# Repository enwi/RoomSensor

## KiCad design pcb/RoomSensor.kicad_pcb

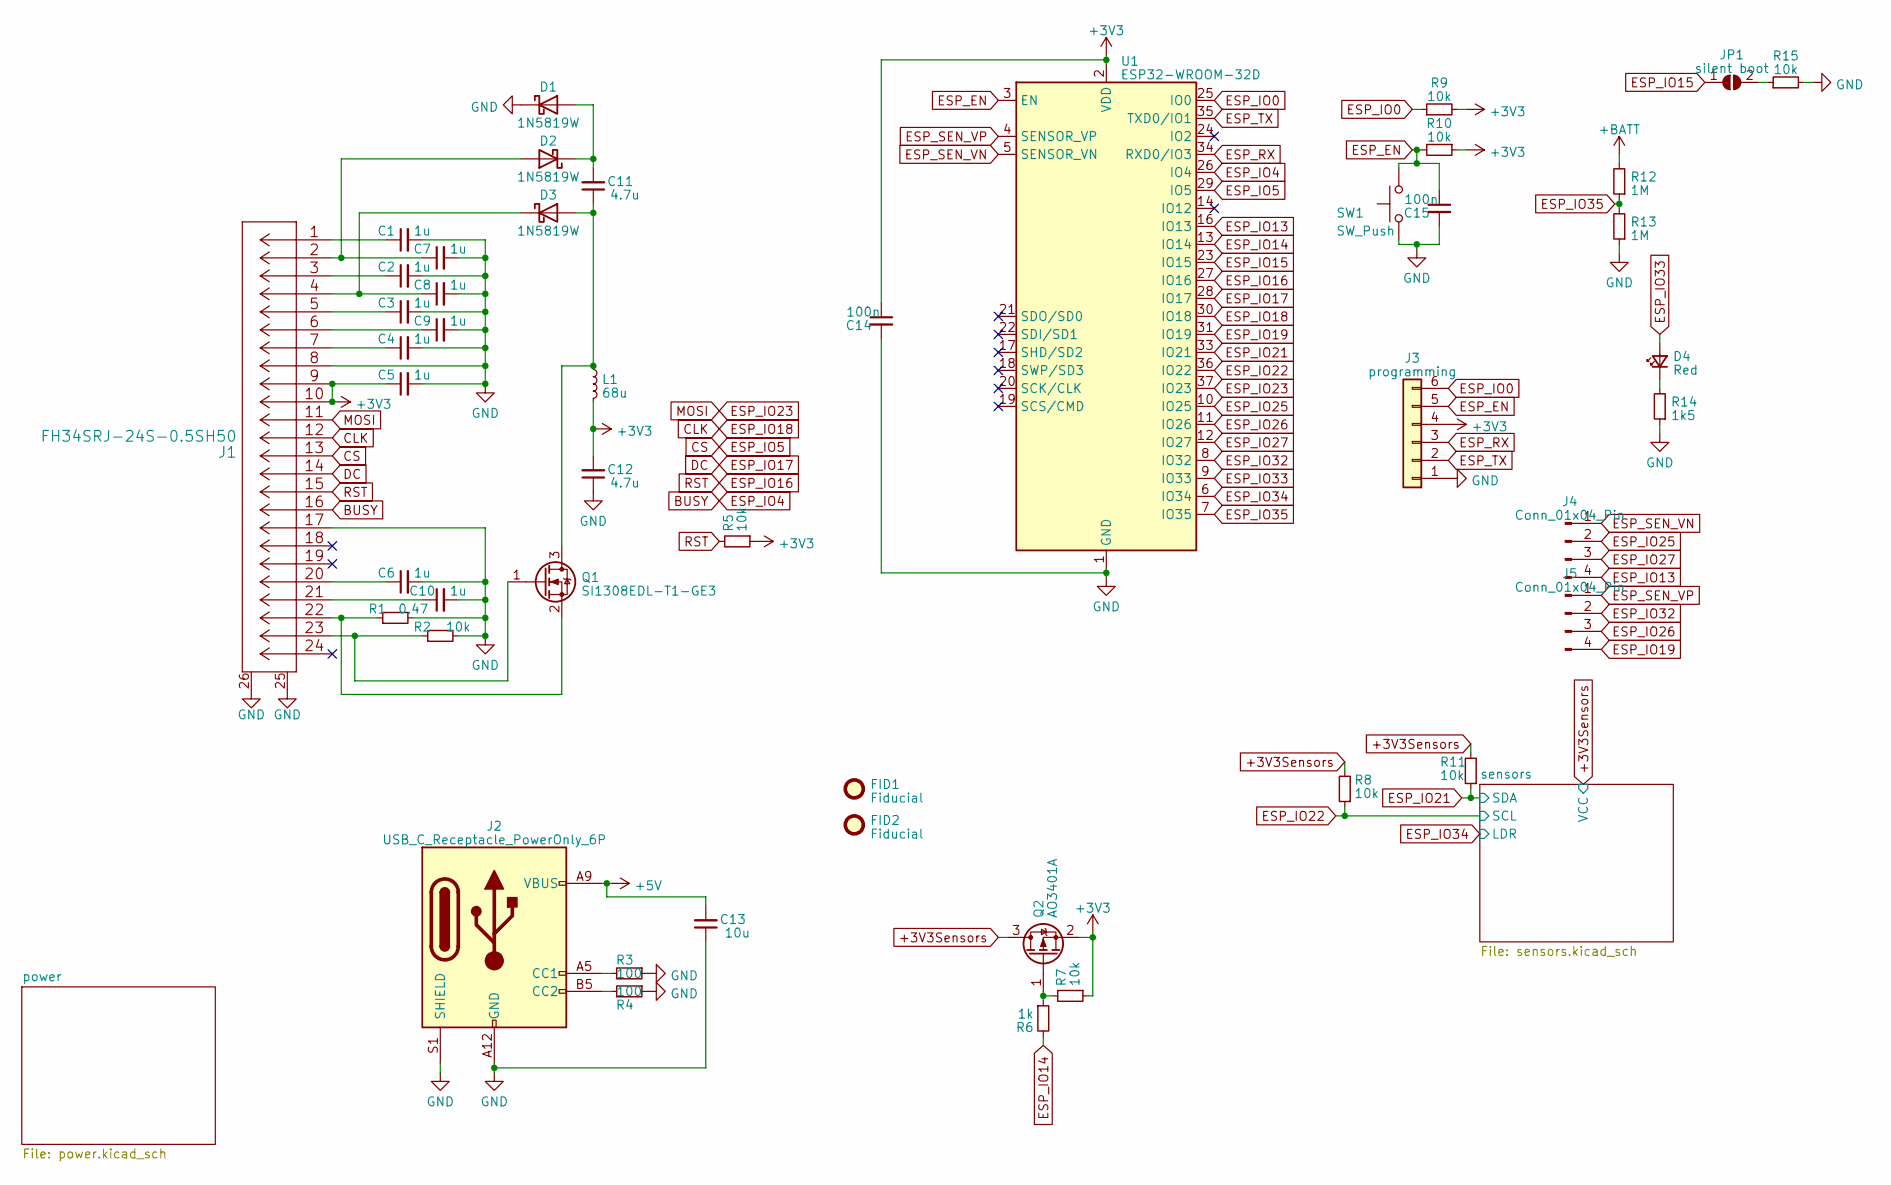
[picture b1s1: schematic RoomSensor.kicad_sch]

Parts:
C1, C2, C3, C4, C5, C6, C7, C8, C9, C10: 1u; C_0603_1608Metric
C11, C12: 4.7u; C_0603_1608Metric
C13: 10u; C_0603_1608Metric
C14, C15: 100n; C_0603_1608Metric
D1, D2, D3: 1N5819W; D_SOD-323
D4: Red; LED_0603_1608Metric
FID1, FID2: Fiducial; Fiducial_0.5mm_Mask1.5mm
J1: FH34SRJ-24S-0.5SH50
J2: USB_C_Receptacle_PowerOnly_6P; TYPE-C 6P LCH10.0
J3: programming; PinSocket_1x06_P2.54mm_Vertical
J4, J5: Conn_01x04_Pin; PinHeader_1x04_P2.54mm_Vertical
JP1: silent boot; SolderJumper-2_P1.3mm_Open_TrianglePad1.0x1.5mm
L1: 68u; L_0805_2012Metric_Pad1.15x1.40mm_HandSolder
Q1: SI1308EDL-T1-GE3; SOT-323_SC-70
Q2: AO3401A; SOT-23
R1: 0.47; R_0603_1608Metric
R2, R5, R7, R8, R9, R10, R11, R15: 10k; R_0603_1608Metric
R3, R4: 100; R_0603_1608Metric
R6: 1k; R_0603_1608Metric
R12, R13: 1M; R_0603_1608Metric
R14: 1k5; R_0603_1608Metric
SW1: SW_Push; TSB001A3826A
U1: ESP32-WROOM-32D

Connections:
+3V3: C5.1, C12.2, C14.1, J1.9, J1.10, J3.4, L1.2, Q2.2 (S), R5.1, R7.1, R9.2, R10.1, U1.2 (VDD); also elsewhere on the board
+3V3Sensors: Q2.3 (D), R8.2, R11.2; also elsewhere on the board
+5V: C13.2, J2.A9 (VBUS), J2.B9 (VBUS); also elsewhere on the board
+BATT: R12.2; also elsewhere on the board
BUSY: J1.16, U1.26 (IO4)
CLK: J1.12, U1.30 (IO18)
CS: J1.13, U1.29 (IO5)
DC: J1.14, U1.28 (IO17)
ESP_EN: C15.1, J3.5, R10.2, SW1.2, U1.3 (EN)
ESP_IO0: J3.6, R9.1, U1.25 (IO0)
ESP_IO13: J4.4, U1.16 (IO13)
ESP_IO14: R6.2, U1.13 (IO14)
ESP_IO15: JP1.1 (A), U1.23 (IO15)
ESP_IO16: J1.15, R5.2, U1.27 (IO16)
ESP_IO19: J5.4, U1.31 (IO19)
ESP_IO21: R11.1, U1.33 (IO21); also elsewhere on the board
ESP_IO22: R8.1, U1.36 (IO22); also elsewhere on the board
ESP_IO23: J1.11, U1.37 (IO23)
ESP_IO25: J4.2, U1.10 (IO25)
ESP_IO26: J5.3, U1.11 (IO26)
ESP_IO27: J4.3, U1.12 (IO27)
ESP_IO32: J5.2, U1.8 (IO32)
ESP_IO33: D4.2 (A), U1.9 (IO33)
ESP_IO34: U1.6 (IO34); also elsewhere on the board
ESP_IO35: R12.1, R13.2, U1.7 (IO35)
ESP_RX: J3.3, U1.34 (RXD0/IO3)
ESP_SEN_VN: J4.1, U1.5 (SENSOR_VN)
ESP_SEN_VP: J5.1, U1.4 (SENSOR_VP)
ESP_TX: J3.2, U1.35 (TXD0/IO1)
GND: C1.2, C2.2, C3.2, C4.2, C5.2, C6.2, C7.2, C8.2, C9.2, C10.2, C12.1, C13.1, C14.2, C15.2, D1.1 (K), J1.8, J1.17, J1.25, J1.26, J2.A12 (GND), J2.B12 (GND), J2.S1 (SHIELD), J3.1, R1.2, R2.2, R3.1, R4.1, R13.1, R14.1, R15.2, SW1.1, U1.1 (GND), U1.15 (GND), U1.38 (GND), U1.39 (GND); also elsewhere on the board
unnamed: C1.1, J1.1
unnamed: C2.1, J1.3
unnamed: C3.1, J1.5
unnamed: C4.1, J1.7
unnamed: C6.1, J1.20
unnamed: C9.1, J1.6
unnamed: C10.1, J1.21
unnamed: C11.2, D1.2 (A), D2.1 (K)
unnamed: C7.1, D2.2 (A), J1.2
unnamed: C11.1, D3.2 (A), L1.1, Q1.3 (D)
unnamed: C8.1, D3.1 (K), J1.4
unnamed: D4.1 (K), R14.2
unnamed: J2.A5 (CC1), R3.2
unnamed: J2.B5 (CC2), R4.2
unnamed: JP1.2 (B), R15.1
unnamed: J1.23, Q1.1 (G), R2.1
unnamed: J1.22, Q1.2 (S), R1.1
unnamed: Q2.1 (G), R6.1, R7.2

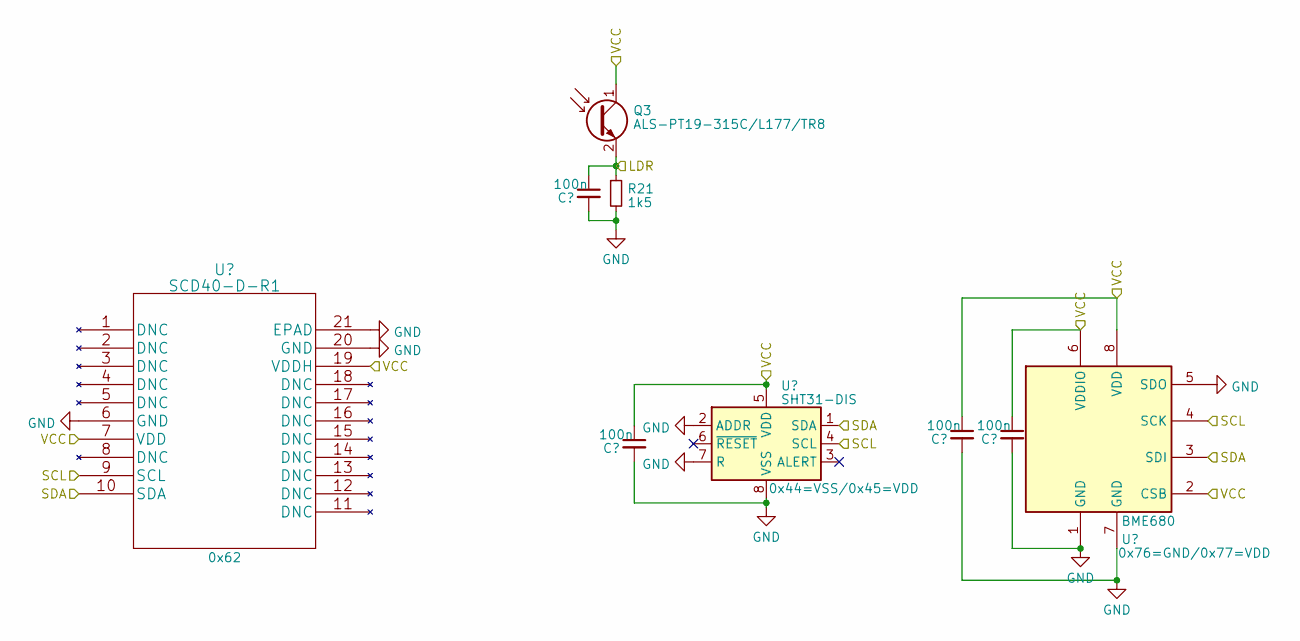
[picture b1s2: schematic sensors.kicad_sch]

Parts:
C21, C22, C23, C24: 100n; C_0603_1608Metric
Q3: ALS-PT19-315C/L177/TR8; LED_0603_1608Metric
R21: 1k5; R_0603_1608Metric
U6: SCD40-D-R1
U7: SHT31-DIS; Sensirion_DFN-8-1EP_2.5x2.5mm_P0.5mm_EP1.1x1.7mm
U8: BME680; Bosch_LGA-8_3x3mm_P0.8mm_ClockwisePinNumbering

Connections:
+3V3Sensors: C22.1, C23.1, C24.1, Q3.1 (C), U6.7 (VDD), U6.19 (VDDH), U7.5 (VDD), U8.2 (CSB), U8.6 (VDDIO), U8.8 (VDD); also elsewhere on the board
ESP_IO21: U6.10 (SDA), U7.1 (SDA), U8.3 (SDI); also elsewhere on the board
ESP_IO22: U6.9 (SCL), U7.4 (SCL), U8.4 (SCK); also elsewhere on the board
ESP_IO34: C21.1, Q3.2 (E), R21.1; also elsewhere on the board
GND: C21.2, C22.2, C23.2, C24.2, R21.2, U6.6 (GND), U6.20 (GND), U6.21 (EPAD), U7.2 (ADDR), U7.7 (R), U7.8 (VSS), U7.9 (VSS), U8.1 (GND), U8.5 (SDO), U8.7 (GND); also elsewhere on the board

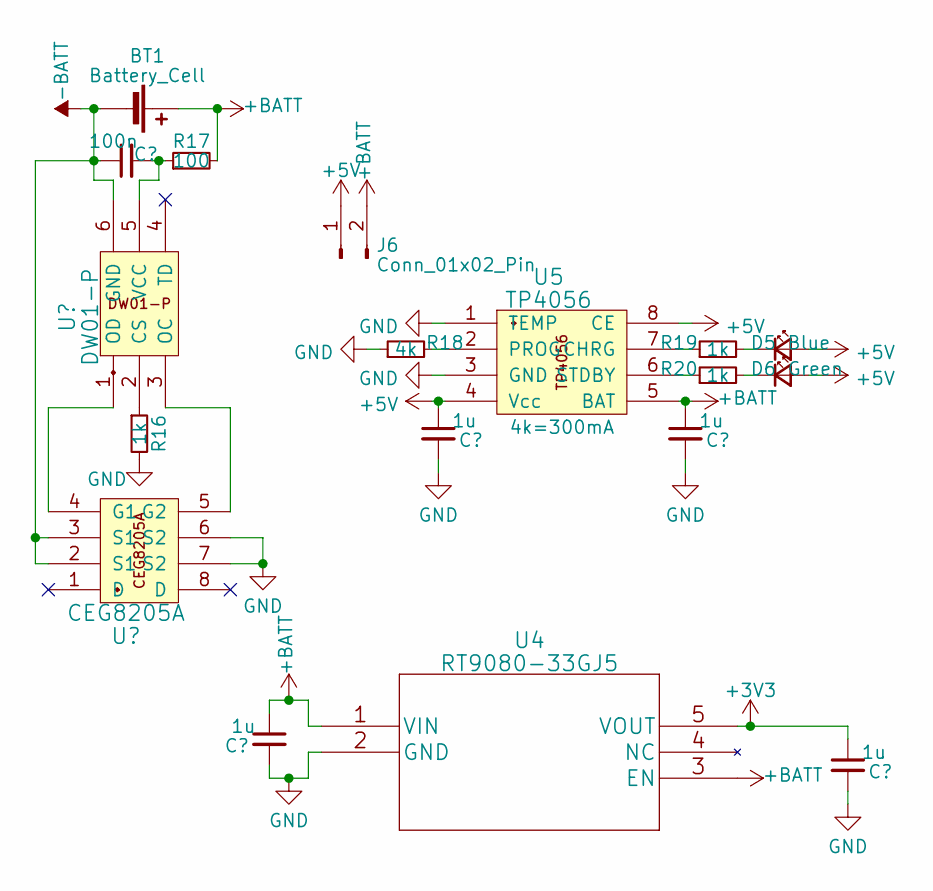
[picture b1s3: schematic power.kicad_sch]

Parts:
BT1: Battery_Cell; PinHeader_1x02_P2.54mm_Vertical
C16: 100n; C_0603_1608Metric
C17, C18, C19, C20: 1u; C_0603_1608Metric
D5: Blue; LED_0603_1608Metric
D6: Green; LED_0603_1608Metric
J6: Conn_01x02_Pin; PinHeader_1x02_P2.54mm_Vertical
R16, R19, R20: 1k; R_0603_1608Metric
R17: 100; R_0603_1608Metric
R18: 4k; R_0603_1608Metric
U2: DW01-P; SOT-23-6
U3: CEG8205A; TSSOP-8_4.4x3mm_P0.65mm
U4: RT9080-33GJ5
U5: TP4056; SOIC-8-1EP_3.9x4.9mm_P1.27mm_EP2.29x3mm_ThermalVias

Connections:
+3V3: C20.1, U4.5 (VOUT); also elsewhere on the board
+5V: C18.1, D5.2 (A), D6.2 (A), J6.1, U5.4 (Vcc), U5.8 (CE); also elsewhere on the board
+BATT: BT1.1 (+), C17.1, C19.1, J6.2, R17.2, U4.1 (VIN), U4.3 (EN), U5.5 (BAT); also elsewhere on the board
-BATT: BT1.2 (-), C16.1, U2.6 (GND), U3.2 (S1), U3.3 (S1)
GND: C17.2, C18.2, C19.2, C20.2, R16.2, R18.1, U3.6 (S2), U3.7 (S2), U4.2 (GND), U5.1 (TEMP), U5.3 (GND), U5.9 (HeatPad); also elsewhere on the board
unnamed: D5.1 (K), R19.2
unnamed: D6.1 (K), R20.2
unnamed: R16.1, U2.2 (CS)
unnamed: U2.3 (OC), U3.5 (G2)
unnamed: U2.1 (OD), U3.4 (G1)
unnamed: C16.2, R17.1, U2.5 (VCC)
unnamed: R19.1, U5.7 (CHRG)
unnamed: R18.2, U5.2 (PROG)
unnamed: R20.1, U5.6 (STDBY)

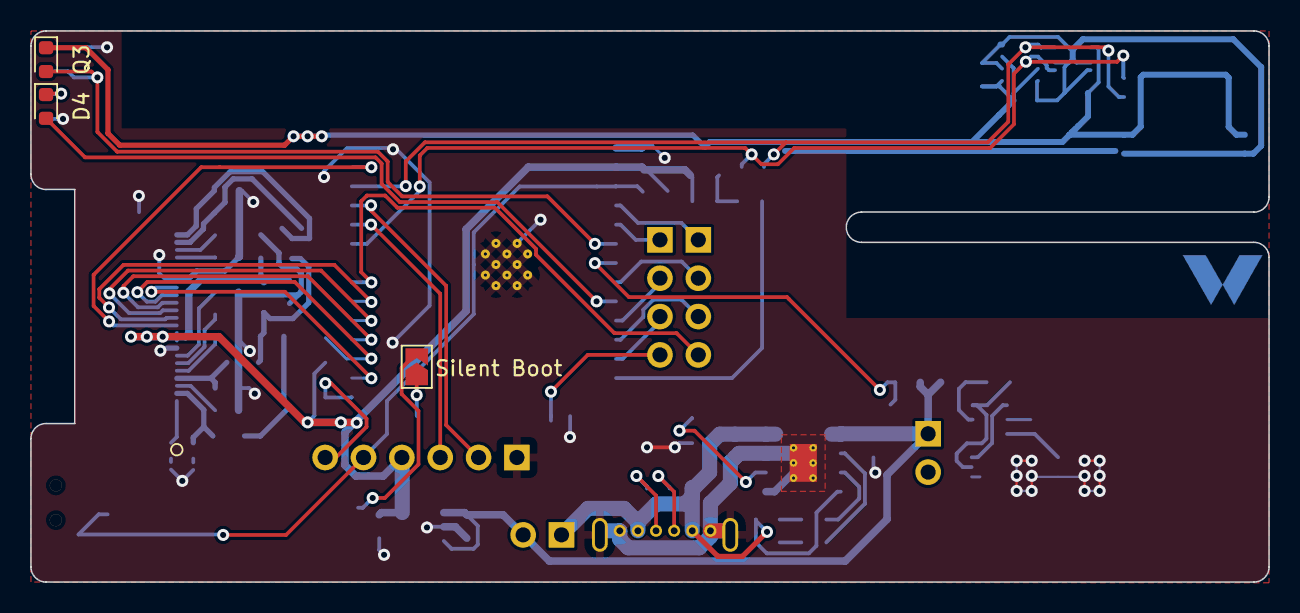
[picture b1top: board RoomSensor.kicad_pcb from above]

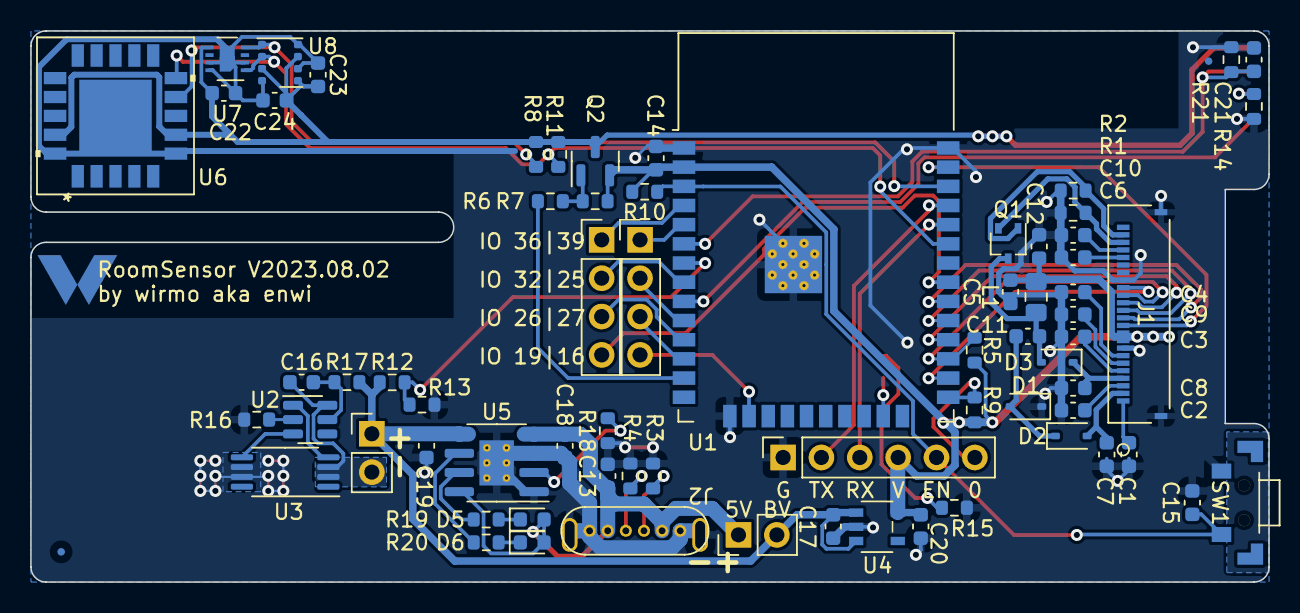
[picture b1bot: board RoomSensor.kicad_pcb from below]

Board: 2 copper layers, 82.0 x 36.5 mm, 74 parts (71 on the bottom side), 58 nets.

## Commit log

2023-02-19 Initial pcb commit
2023-02-25 Increase PCB size and fix EPD pinout
2023-04-01 Ignore build and gerber files
2023-04-01 Fix low power issues
    - Fix spurious EPD wakeups by adding pull-up to EPD reset line
    - Reduce power consumption by switching sensors off with mosfet
    - Connect button to reset to reduce power by not needing rtc gpio
    - Add solder jumper for silent boot
2023-04-01 Ignore gerber, bom and report files
2023-07-30 Replace b- net with -Battery
2023-08-02 Move epd connector and fix net
2023-08-05 Initial code commit
2023-08-05 Add config file
2023-08-05 Add mqtt config into Config.h
2023-08-05 Add missing HomeAssistant.h file
2023-08-06 Remove unused code
    - Move mqtt discovery code into key
    - Improve HA code
    - Add software version to config
2023-08-06 Fix auto discovery and also publish battery voltage
    - Tweak battery voltage conversion
2023-08-27 Store boot count in slow rtc memory
2023-08-27 Use PIO
2023-10-15 Change cpu frequency to 80MHz

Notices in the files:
parts and their libraries:
Copyright 2021 Accelerated Designs. All rights reserved.
